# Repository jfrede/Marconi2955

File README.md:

# Marconi 2955 – open firmware

Goal: a functionally equivalent, open re-implementation of the firmware of the Marconi 2955
radio communications test set, with bug fixes and convenience features (quick frequency entry,
user-defined power-on default, plain-text self-test error messages).

## Layout
- `docs/`   – hardware and behaviour specification (own text, publishable)
- `emu/`    – 8085 emulator and instrument peripherals (C)
- `fw/`     – new firmware (C, platform-neutral with a hardware abstraction layer)
- `tools/`  – helper scripts for building and comparing
- `hardware/` – KiCad projects of the add-on boards
- `private/` – original ROMs, manuals, Ghidra project, disassembly. **Not in the repository.**

## Documentation
Start with [docs/architecture.md](docs/architecture.md). The other files in `docs/` explain how
each function works, the registers, the stored data, GPIB, and what is still missing.

## Rules
- Original ROMs, their disassembly and the manual PDFs stay private (see `.gitignore`).
- Only own code and self-written specification are published.
- Before any test on the instrument: back up EEPROM IC13. It holds the calibration data, which
  cannot be recreated. The NOVRAMs hold only the current settings; GPIB `SV` reads them out if
  you want to keep them.

## Licence

- `fw/`, `emu/` and `tools/`: GNU General Public License, version 3 or later (GPL-3.0-or-later). See [LICENSE](LICENSE).
- `docs/`: Creative Commons Attribution 4.0 International (CC BY 4.0). See [docs/LICENSE](docs/LICENSE).
- `hardware/`: CERN Open Hardware Licence Version 2, Strongly Reciprocal (CERN-OHL-S-2.0). See [hardware/LICENSE](hardware/LICENSE).

Original ROMs and manuals are not part of this project and are not covered by these licences.

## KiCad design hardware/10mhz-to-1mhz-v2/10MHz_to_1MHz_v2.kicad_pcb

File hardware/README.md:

# Hardware

Add-on boards for the Marconi 2955, as KiCad projects with Gerber files.

| Folder | Board |
|---|---|
| `step-attenuator/` | Solid-state replacement for the coarse step attenuator |
| `om345-replacement/` | Replacement for the OM345 hybrid amplifier, using a MAR-7SM+ |
| `om345-testrig/` | Test fixture for measuring an OM345 or a replacement board |
| `10mhz-to-1mhz/` | Converts a 10 MHz reference signal to 1 MHz |
| `10mhz-to-1mhz-v2/` | Redesign of the converter with SMD parts and a single 5 V supply (v2.0, not built or tested yet; see its SPEC.md) |
| `cpu-adapter/` | RP2354B board for the 8085 socket, runs the new firmware (v1.0, not built or tested yet; see its SPEC.md) |

## Pictures

### Step attenuator

### OM345 replacement

### 10 MHz to 1 MHz converter

The picture shows the first version, with through-hole parts. It uses a 74LS90, a 2N2369 and a
BC308B and needs -12 V besides +5 V. The second version uses a TLV3501 comparator and a 74HC390
and runs from +5 V alone. Specification and status:
[10mhz-to-1mhz-v2/SPEC.md](10mhz-to-1mhz-v2/SPEC.md).

### CPU adapter

The RP2354B board that replaces the 8085 on AB4. Specification and status:
[cpu-adapter/SPEC.md](cpu-adapter/SPEC.md).

## Licence

The board designs in this folder are open hardware under the CERN Open Hardware Licence
Version 2, Strongly Reciprocal (CERN-OHL-S-2.0). See [LICENSE](LICENSE).

## Note on the MAR-7SM+ footprint

The symbol and footprint library for the MAR-7SM+ is not included, because its licence does not
allow it to be passed on as a library. It comes from SamacSys. The board file still contains the
footprint, so the board opens and can be fabricated as it is. To change the footprint, get the
library for the MAR-7SM+ yourself and add it to the project as a library called `RF`.

## Note on the CPU adapter's libraries and 3D models

The KiCad library for the SN74LVC16245ADGGR (from TI) and the STEP models for the RP2354B, the
TSSOP-48 translators and the USB-C receptacle are not included, because their licences are
unclear or do not allow them to be passed on. The board file still contains all footprints, so
the board opens and can be fabricated as it is; only the 3D view lacks those parts.

## Note on the SMA jacks of the 10 MHz to 1 MHz converter v2

The STEP model of the Amphenol 901-143 SMA jack (`901-143.STEP`, referred to from the project
folder) is not included, because its licence is unclear. Only the 3D view lacks the two jacks.

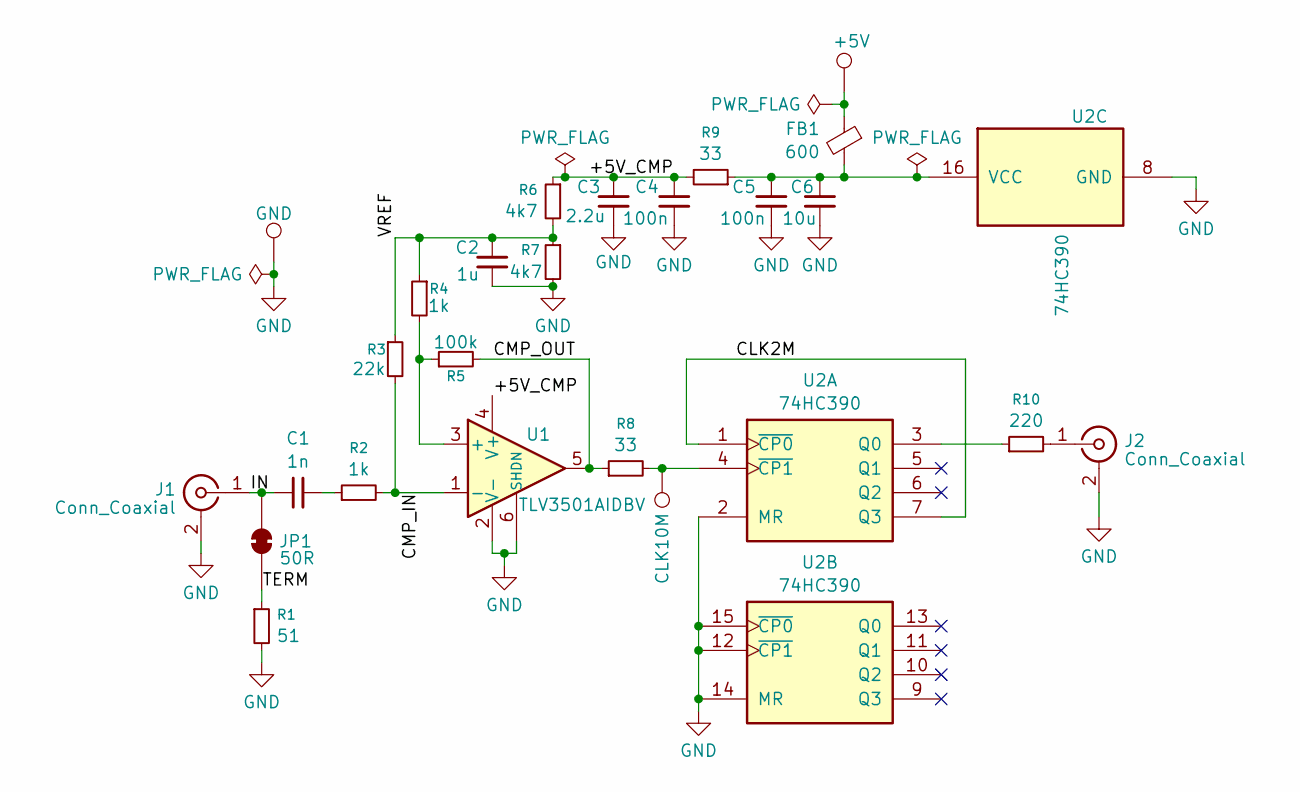
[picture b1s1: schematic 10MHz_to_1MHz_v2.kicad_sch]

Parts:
C1: 1n; C_0603_1608Metric_Pad1.08x0.95mm_HandSolder
C2: 1u; C_0603_1608Metric_Pad1.08x0.95mm_HandSolder
C3: 2.2u; C_0603_1608Metric_Pad1.08x0.95mm_HandSolder
C4, C5: 100n; C_0603_1608Metric_Pad1.08x0.95mm_HandSolder
C6: 10u; C_0805_2012Metric_Pad1.18x1.45mm_HandSolder
FB1: 600; L_0805_2012Metric_Pad1.05x1.20mm_HandSolder
J1, J2: Conn_Coaxial; SMA_Amphenol_901-143_Horizontal
JP1: 50R; SolderJumper-2_P1.3mm_Bridged_Pad1.0x1.5mm
R1: 51; R_0805_2012Metric_Pad1.20x1.40mm_HandSolder
R2, R4: 1k; R_0603_1608Metric_Pad0.98x0.95mm_HandSolder
R3: 22k; R_0603_1608Metric_Pad0.98x0.95mm_HandSolder
R5: 100k; R_0603_1608Metric_Pad0.98x0.95mm_HandSolder
R6, R7: 4k7; R_0603_1608Metric_Pad0.98x0.95mm_HandSolder
R8, R9: 33; R_0603_1608Metric_Pad0.98x0.95mm_HandSolder
R10: 220; R_0603_1608Metric_Pad0.98x0.95mm_HandSolder
TP1: +5V; TestPoint_THTPad_D2.0mm_Drill1.0mm
TP2: GND; TestPoint_THTPad_D2.0mm_Drill1.0mm
TP3: CLK10M; TestPoint_Pad_D1.0mm
U1: TLV3501AIDBV; SOT-23-6
U2: 74HC390; SO-16_3.9x9.9mm_P1.27mm

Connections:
/+5V_CMP: C3.2, C4.2, R6.1, R9.2, U1.4 (V+)
/CLK2M: U2.1 (~CP0), U2.7 (Q3)
/CMP_IN: R2.2, R3.2, U1.1 (-)
/CMP_OUT: R5.2, R8.1, U1.5
/IN: C1.1, J1.1 (In), JP1.2 (B)
/TERM: JP1.1 (A), R1.1
/VREF: C2.2, R3.1, R4.1, R6.2, R7.1
GND: C2.1, C3.1, C4.1, C5.1, C6.1, J1.2 (Ext), J2.2 (Ext), R1.2, R7.2, TP2.1 (1_1), U1.2 (V-), U1.6 (SHDN), U2.2 (MR), U2.8 (GND), U2.12 (~CP1), U2.14 (MR), U2.15 (~CP0)
unnamed: C1.2, R2.1
unnamed: FB1.1, TP1.1 (1_1)
unnamed: J2.1 (In), R10.2
unnamed: R4.2, R5.1, U1.3 (+)
unnamed: R10.1, U2.3 (Q0)
unnamed: R8.2, TP3.1 (1_1), U2.4 (~CP1)
unnamed: C5.2, C6.2, FB1.2, R9.1, U2.16 (VCC)

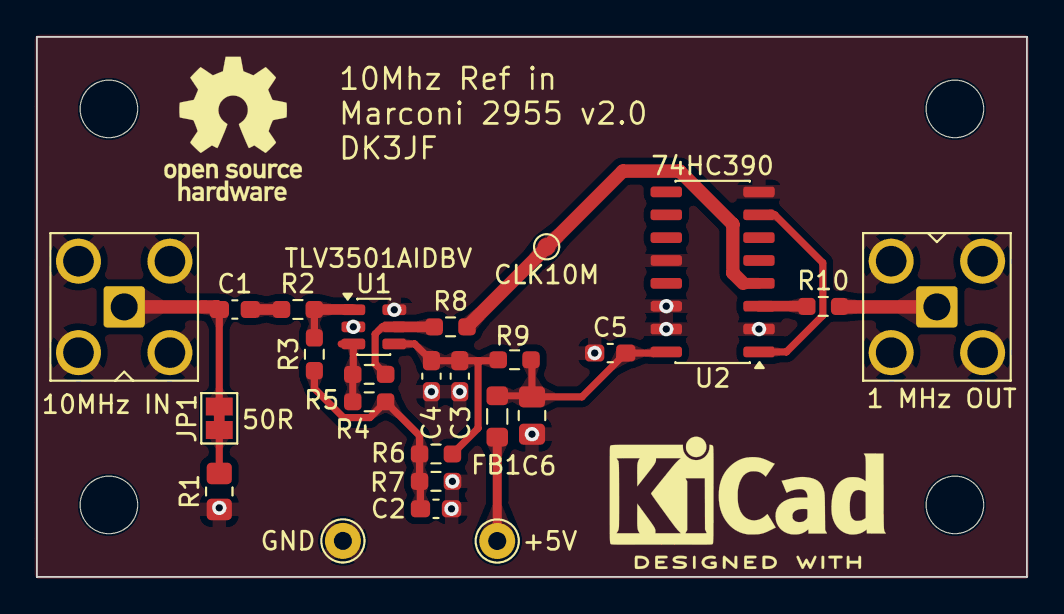
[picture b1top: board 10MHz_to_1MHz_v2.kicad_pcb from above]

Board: 2 copper layers, 55.0 x 30.0 mm, 25 parts (0 on the bottom side), 15 nets.

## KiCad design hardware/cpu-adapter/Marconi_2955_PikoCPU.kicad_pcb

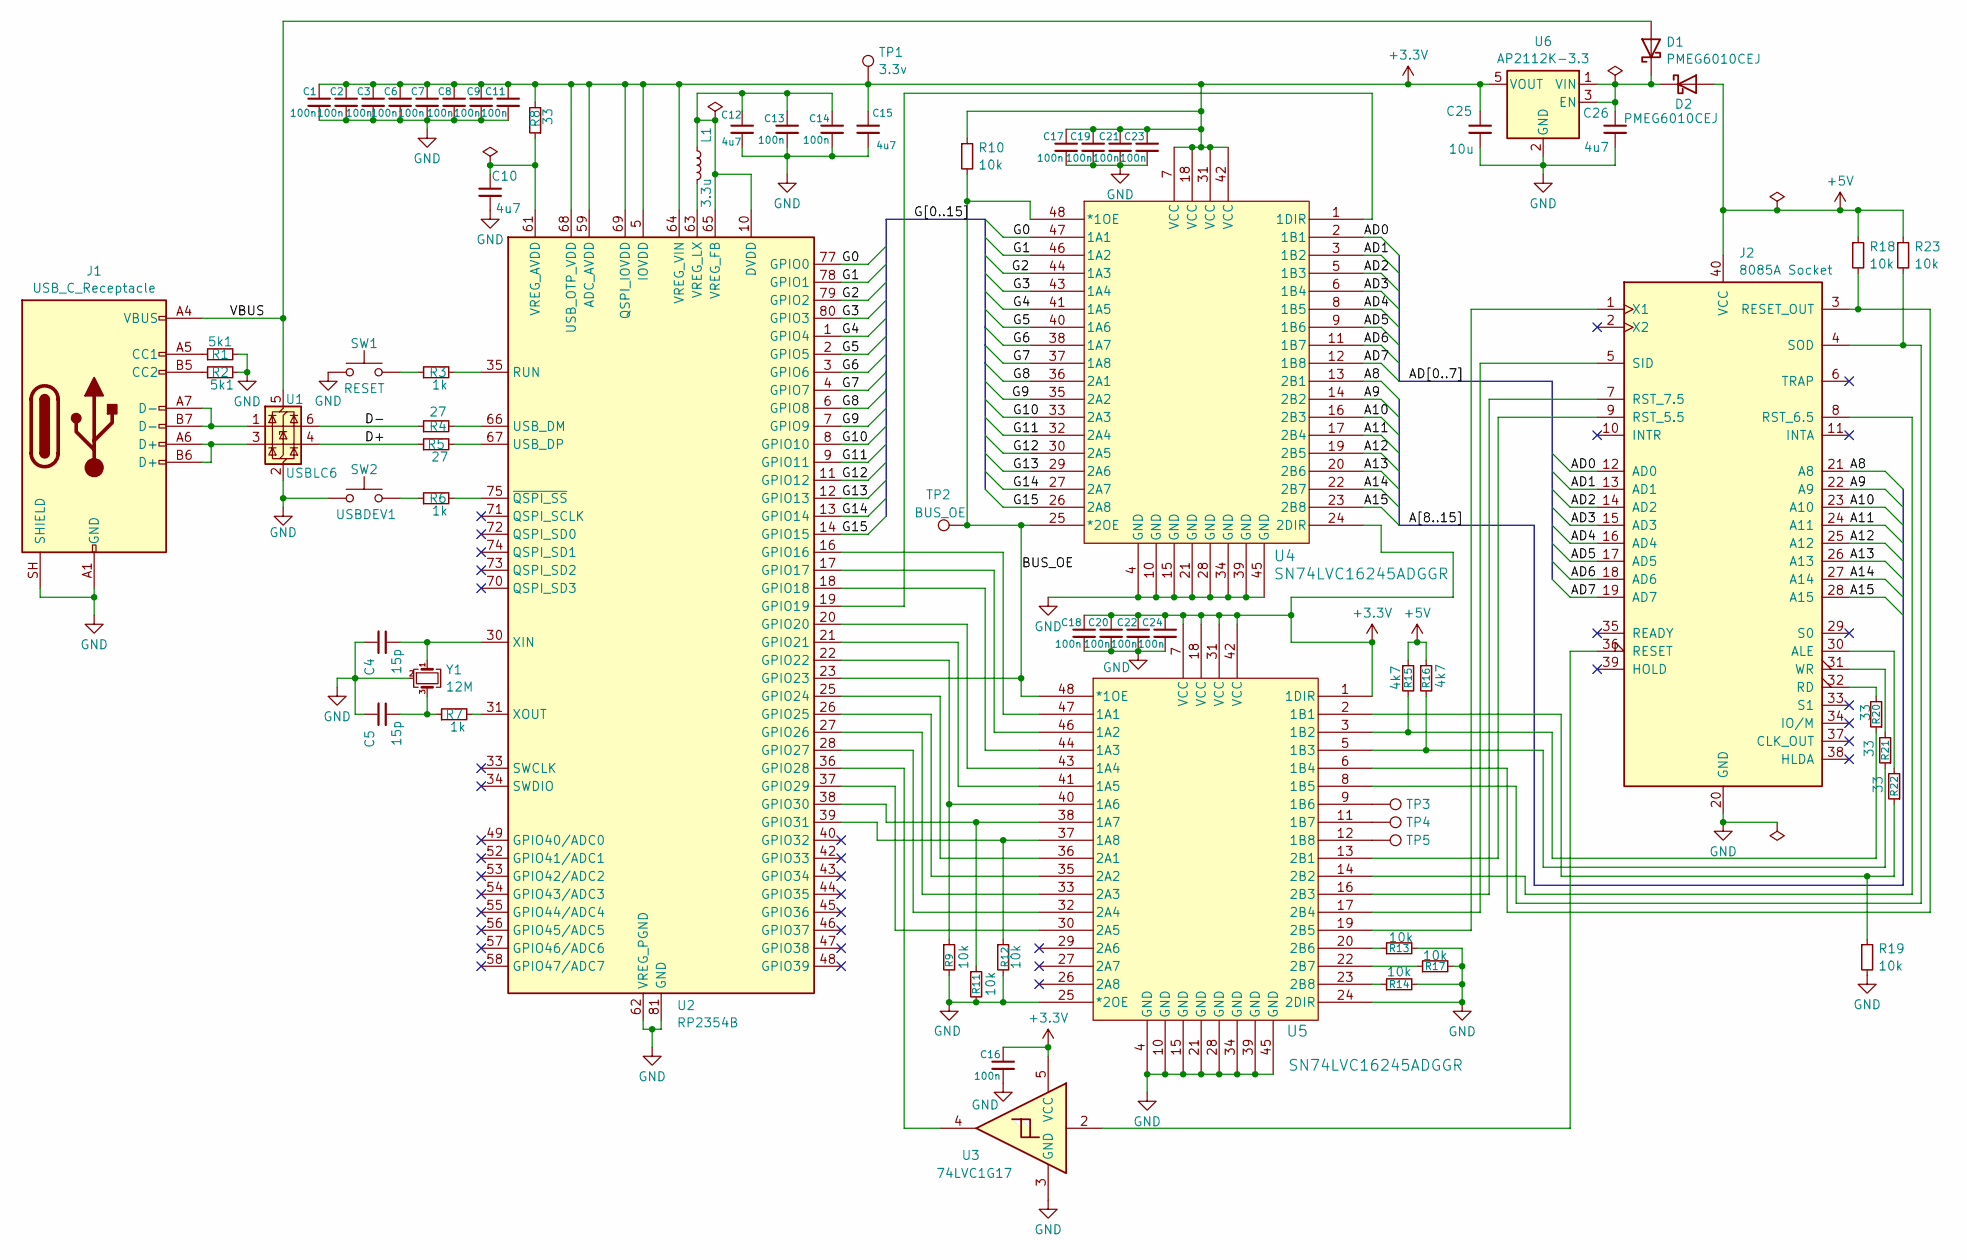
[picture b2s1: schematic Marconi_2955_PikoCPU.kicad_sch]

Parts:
C1, C2, C3, C6, C7, C8, C9, C11, C13, C14, C16, C17, C18, C19, C20, C21, C22, C23, C24: 100n; C_0603_1608Metric_Pad1.08x0.95mm_HandSolder
C4, C5: 15p; C_0603_1608Metric_Pad1.08x0.95mm_HandSolder
C10, C12, C15, C26: 4u7; C_0805_2012Metric_Pad1.18x1.45mm_HandSolder
C25: 10u; C_1210_3225Metric_Pad1.33x2.70mm_HandSolder
D1, D2: PMEG6010CEJ; D_SOD-323
J1: USB_C_Receptacle; USB_C_Receptacle_HRO_TYPE-C-31-M-12
J2: 8085A Socket; DIP-40_W15.24mm
L1: 3.3u; L_0805_2012Metric_Pad1.05x1.20mm_HandSolder
R1, R2: 5k1; R_0603_1608Metric_Pad0.98x0.95mm_HandSolder
R3, R6, R7: 1k; R_0603_1608Metric_Pad0.98x0.95mm_HandSolder
R4, R5: 27; R_0603_1608Metric_Pad0.98x0.95mm_HandSolder
R8, R20, R21, R22: 33; R_0603_1608Metric_Pad0.98x0.95mm_HandSolder
R9, R10, R11, R12, R13, R14, R17, R18, R19, R23: 10k; R_0603_1608Metric_Pad0.98x0.95mm_HandSolder
R15, R16: 4k7; R_0603_1608Metric_Pad0.98x0.95mm_HandSolder
SW1: RESET; SW_SPST_PTS810
SW2: USBDEV1; SW_SPST_PTS810
TP1: 3.3v; TestPoint_Pad_D1.0mm
TP2: BUS_OE; TestPoint_Pad_D1.0mm
TP3, TP4, TP5: TestPoint_Pad_D1.0mm
U1: USBLC6; SOT-23-6
U2: RP2354B; QFN-80-1EP_10x10mm_P0.4mm_EP3.4x3.4mm
U3: 74LVC1G17; SOT-23-5_HandSoldering
U4, U5: SN74LVC16245ADGGR; DGG48
U6: AP2112K-3.3; SOT-23-5
Y1: 12M; Crystal_SMD_3225-4Pin_3.2x2.5mm

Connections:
+3.3V: C1.1, C2.1, C3.1, C6.1, C7.1, C8.1, C9.1, C11.1, C15.2, C16.1, C17.1, C18.1, C19.1, C20.1, C21.1, C22.1, C23.1, C24.1, C25.1, R8.2, R10.1, TP1.1 (1_1), U2.5 (IOVDD), U2.15 (IOVDD), U2.24 (IOVDD), U2.29 (IOVDD), U2.41 (IOVDD), U2.50 (IOVDD), U2.59 (ADC_AVDD), U2.60 (IOVDD), U2.64 (VREG_VIN), U2.68 (USB_OTP_VDD), U2.69 (QSPI_IOVDD), U2.76 (IOVDD), U3.5 (VCC), U4.7 (VCC), U4.18 (VCC), U4.24 (2DIR), U4.31 (VCC), U4.42 (VCC), U5.1 (1DIR), U5.7 (VCC), U5.18 (VCC), U5.31 (VCC), U5.42 (VCC), U6.5 (VOUT)
+5V: D2.2 (A), J2.40 (VCC), R15.1, R16.1, R18.1, R23.1
/A8: J2.21 (A8), U4.13 (2B1)
/A9: J2.22 (A9), U4.14 (2B2)
/A10: J2.23 (A10), U4.16 (2B3)
/A11: J2.24 (A11), U4.17 (2B4)
/A12: J2.25 (A12), U4.19 (2B5)
/A13: J2.26 (A13), U4.20 (2B6)
/A14: J2.27 (A14), U4.22 (2B7)
/A15: J2.28 (A15), U4.23 (2B8)
/AD0: J2.12 (AD0), U4.2 (1B1)
/AD1: J2.13 (AD1), U4.3 (1B2)
/AD2: J2.14 (AD2), U4.5 (1B3)
/AD3: J2.15 (AD3), U4.6 (1B4)
/AD4: J2.16 (AD4), U4.8 (1B5)
/AD5: J2.17 (AD5), U4.9 (1B6)
/AD6: J2.18 (AD6), U4.11 (1B7)
/AD7: J2.19 (AD7), U4.12 (1B8)
/BUS_OE: R10.2, TP2.1 (1_1), U2.23 (GPIO23), U4.25 (*2OE), U4.48 (*1OE), U5.48 (*1OE)
/D+: R5.1, U1.4 (I/O2)
/D-: R4.1, U1.6 (I/O1)
/G0: U2.77 (GPIO0), U4.47 (1A1)
/G1: U2.78 (GPIO1), U4.46 (1A2)
/G2: U2.79 (GPIO2), U4.44 (1A3)
/G3: U2.80 (GPIO3), U4.43 (1A4)
/G4: U2.1 (GPIO4), U4.41 (1A5)
/G5: U2.2 (GPIO5), U4.40 (1A6)
/G6: U2.3 (GPIO6), U4.38 (1A7)
/G7: U2.4 (GPIO7), U4.37 (1A8)
/G8: U2.6 (GPIO8), U4.36 (2A1)
/G9: U2.7 (GPIO9), U4.35 (2A2)
/G10: U2.8 (GPIO10), U4.33 (2A3)
/G11: U2.9 (GPIO11), U4.32 (2A4)
/G12: U2.11 (GPIO12), U4.30 (2A5)
/G13: U2.12 (GPIO13), U4.29 (2A6)
/G14: U2.13 (GPIO14), U4.27 (2A7)
/G15: U2.14 (GPIO15), U4.26 (2A8)
/VBUS: D1.2 (A), J1.A4 (VBUS), J1.A9 (VBUS), J1.B4 (VBUS), J1.B9 (VBUS), U1.5 (VBUS)
GND: C1.2, C2.2, C3.2, C4.1, C5.1, C6.2, C7.2, C8.2, C9.2, C10.1, C11.2, C12.1, C13.2, C14.2, C15.1, C16.2, C17.2, C18.2, C19.2, C20.2, C21.2, C22.2, C23.2, C24.2, C25.2, C26.2, J1.A1 (GND), J1.A12 (GND), J1.B1 (GND), J1.B12 (GND), J1.SH (SHIELD), J2.20 (GND), R1.2, R2.2, R9.2, R11.2, R12.2, R13.2, R14.2, R17.2, R19.2, SW1.1, SW2.1, U1.2 (GND), U2.62 (VREG_PGND), U2.81 (GND), U3.3 (GND), U4.4 (GND), U4.10 (GND), U4.15 (GND), U4.21 (GND), U4.28 (GND), U4.34 (GND), U4.39 (GND), U4.45 (GND), U5.4 (GND), U5.10 (GND), U5.15 (GND), U5.21 (GND), U5.24 (2DIR), U5.25 (*2OE), U5.28 (GND), U5.34 (GND), U5.39 (GND), U5.45 (GND), U6.2 (GND), Y1.2 (G), Y1.4 (G)
unnamed: C5.2, R7.1, Y1.3
unnamed: C26.1, D1.1 (K), D2.1 (K), U6.1 (VIN), U6.3 (EN)
unnamed: J1.A5 (CC1), R1.1
unnamed: J1.B5 (CC2), R2.1
unnamed: J1.A6 (D+), J1.B6 (D+), U1.3 (I/O2)
unnamed: J1.A7 (D-), J1.B7 (D-), U1.1 (I/O1)
unnamed: J2.30 (ALE), R22.2
unnamed: J2.32 (RD), R20.2
unnamed: J2.36 (RESET), U3.2
unnamed: J2.3 (RESET_OUT), R18.2, U5.6 (1B4)
unnamed: J2.9 (RST_5.5), U5.13 (2B1)
unnamed: J2.8 (RST_6.5), U5.14 (2B2)
unnamed: J2.7 (RST_7.5), U5.16 (2B3)
unnamed: J2.5 (SID), U5.17 (2B4)
unnamed: J2.4 (SOD), R23.2, U5.8 (1B5)
unnamed: J2.31 (WR), R21.2
unnamed: J2.1 (X1), U5.19 (2B5)
unnamed: R3.1, SW1.2
unnamed: R6.1, SW2.2
unnamed: U2.16 (GPIO16), U5.47 (1A1)
unnamed: U2.17 (GPIO17), U5.46 (1A2)
unnamed: U2.18 (GPIO18), U5.44 (1A3)
unnamed: U2.19 (GPIO19), U4.1 (1DIR)
unnamed: U2.20 (GPIO20), U5.43 (1A4)
unnamed: U2.21 (GPIO21), U5.41 (1A5)
unnamed: R9.1, U2.22 (GPIO22), U5.40 (1A6)
unnamed: U2.25 (GPIO24), U5.36 (2A1)
unnamed: U2.26 (GPIO25), U5.35 (2A2)
unnamed: U2.27 (GPIO26), U5.33 (2A3)
unnamed: U2.28 (GPIO27), U5.32 (2A4)
unnamed: U2.36 (GPIO28), U3.4
unnamed: U2.37 (GPIO29), U5.30 (2A5)
unnamed: R11.1, U2.38 (GPIO30), U5.38 (1A7)
unnamed: R12.1, U2.39 (GPIO31), U5.37 (1A8)
unnamed: R3.2, U2.35 (RUN)
unnamed: R4.2, U2.66 (USB_DM)
unnamed: R5.2, U2.67 (USB_DP)
unnamed: C10.2, R8.1, U2.61 (VREG_AVDD)
unnamed: C12.2, C13.1, C14.1, L1.1, U2.10 (DVDD), U2.32 (DVDD), U2.51 (DVDD), U2.65 (VREG_FB)
unnamed: L1.2, U2.63 (VREG_LX)
unnamed: C4.2, U2.30 (XIN), Y1.1
unnamed: R7.2, U2.31 (XOUT)
unnamed: R6.2, U2.75 (~QSPI_SS)
unnamed: R19.1, R22.1, U5.2 (1B1)
unnamed: R15.2, R20.1, U5.3 (1B2)
unnamed: R16.2, R21.1, U5.5 (1B3)
unnamed: TP3.1 (1_1), U5.9 (1B6)
unnamed: TP4.1 (1_1), U5.11 (1B7)
unnamed: TP5.1 (1_1), U5.12 (1B8)
unnamed: R13.1, U5.20 (2B6)
unnamed: R17.1, U5.22 (2B7)
unnamed: R14.1, U5.23 (2B8)

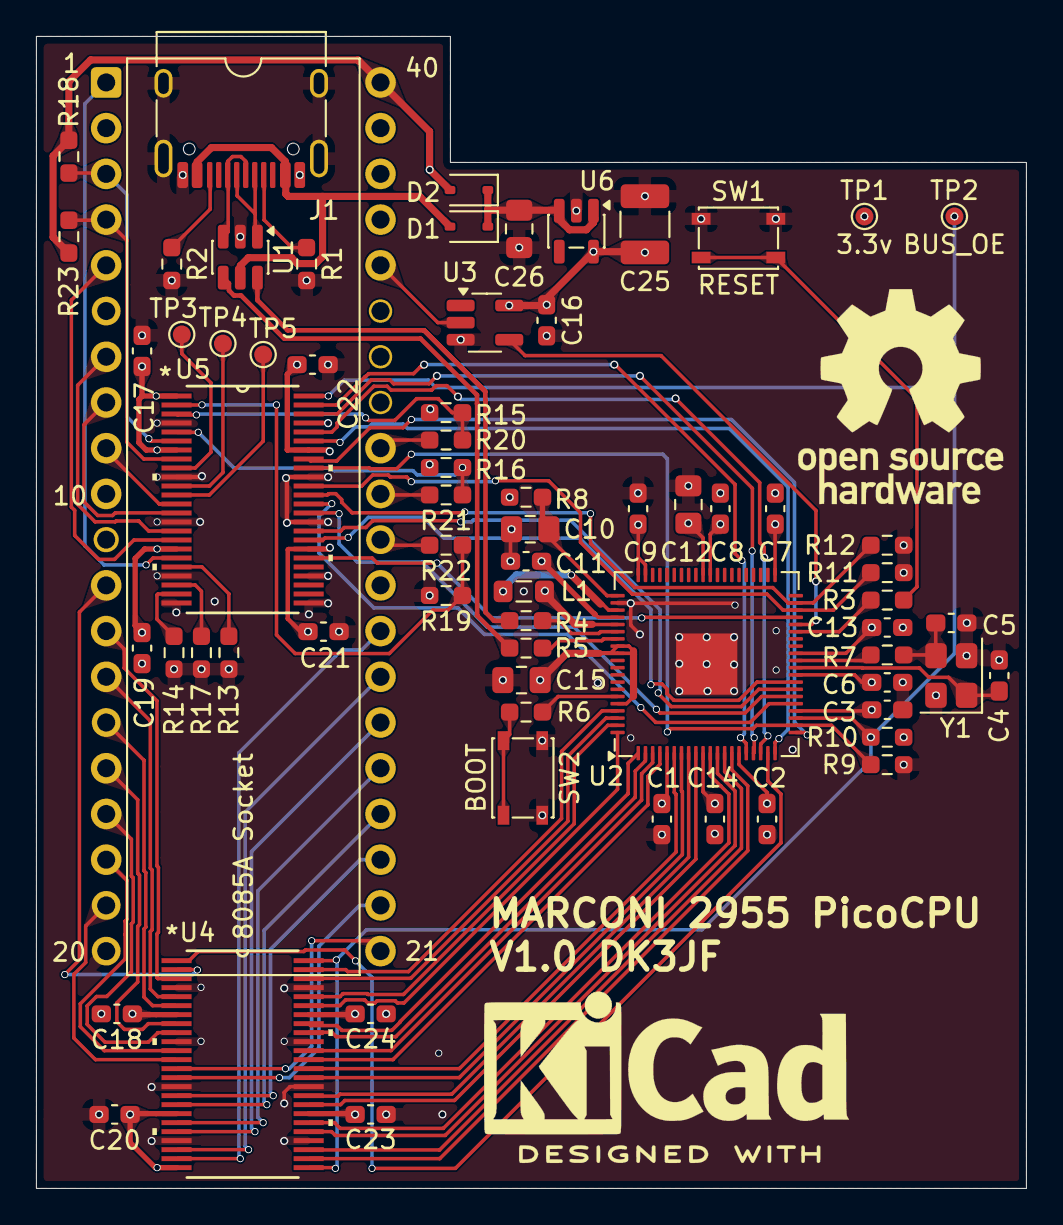
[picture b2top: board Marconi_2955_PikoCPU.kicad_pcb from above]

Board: 4 copper layers, 55.0 x 64.0 mm, 68 parts (0 on the bottom side), 91 nets.

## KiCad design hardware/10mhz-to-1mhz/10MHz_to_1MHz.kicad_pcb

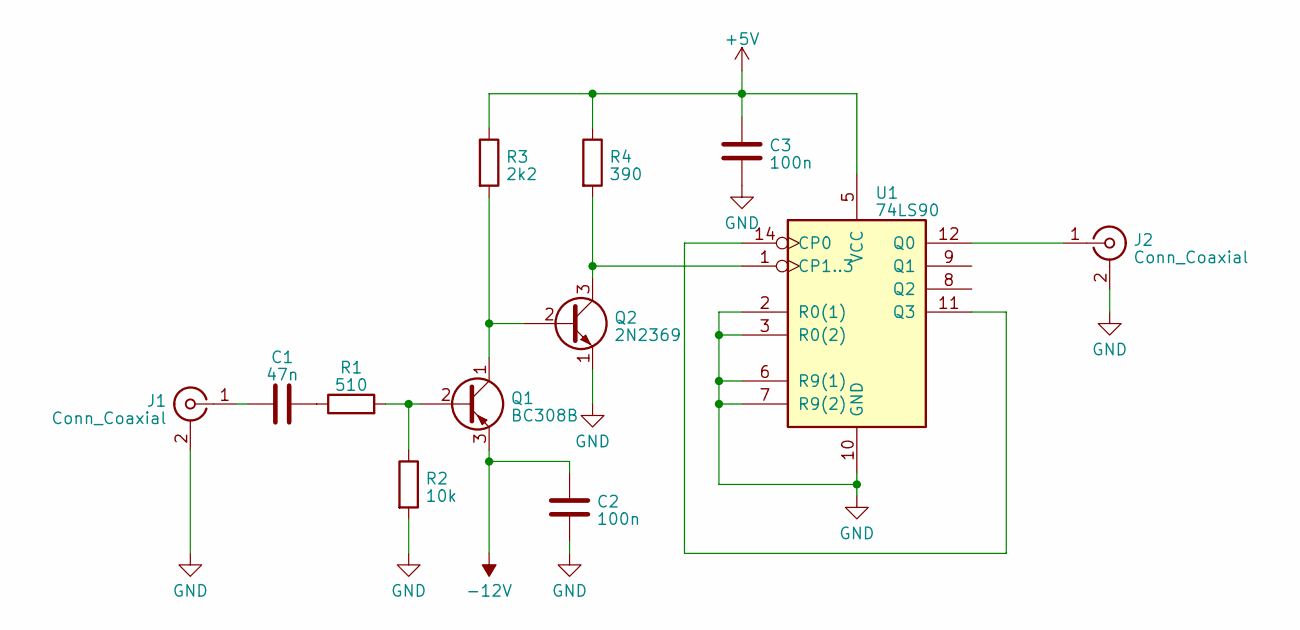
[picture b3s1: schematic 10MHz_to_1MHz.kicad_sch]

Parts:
C1: 47n; C_Disc_D4.7mm_W2.5mm_P5.00mm
C2, C3: 100n; C_Disc_D4.7mm_W2.5mm_P5.00mm
J1, J2: Conn_Coaxial; SMA_Amphenol_901-143_Horizontal
Q1: BC308B; TO-92_Inline
Q2: 2N2369; TO-39-3
R1: 510; R_Axial_DIN0207_L6.3mm_D2.5mm_P10.16mm_Horizontal
R2: 10k; R_Axial_DIN0207_L6.3mm_D2.5mm_P10.16mm_Horizontal
R3: 2k2; R_Axial_DIN0207_L6.3mm_D2.5mm_P10.16mm_Horizontal
R4: 390; R_Axial_DIN0207_L6.3mm_D2.5mm_P10.16mm_Horizontal
U1: 74LS90; DIP-14_W7.62mm

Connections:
+5V: C3.1, R3.1, R4.1, U1.5 (VCC)
-12V: C2.1, Q1.3 (E)
GND: C2.2, C3.2, J1.2 (Ext), J2.2 (Ext), Q2.1 (E), R2.2, U1.2 (R0(1)), U1.3 (R0(2)), U1.6 (R9(1)), U1.7 (R9(2)), U1.10 (GND)
unnamed: C1.2, R1.1
unnamed: C1.1, J1.1 (In)
unnamed: J2.1 (In), U1.12 (Q0)
unnamed: Q1.2 (B), R1.2, R2.1
unnamed: Q1.1 (C), Q2.2 (B), R3.2
unnamed: Q2.3 (C), R4.2, U1.1 (CP1..3)
unnamed: U1.11 (Q3), U1.14 (CP0)

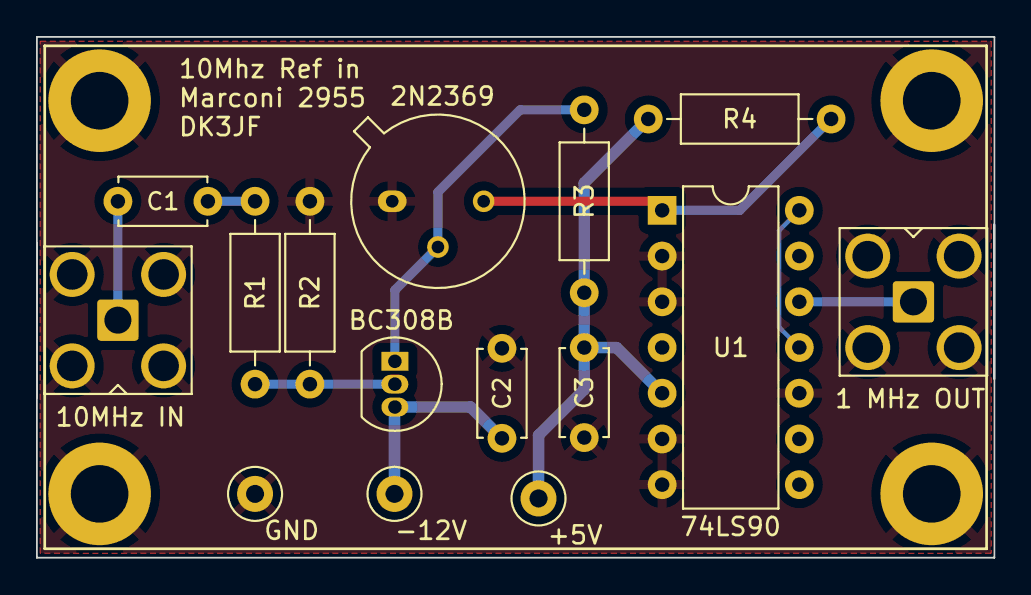
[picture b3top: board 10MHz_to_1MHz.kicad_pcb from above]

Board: 2 copper layers, 53.2 x 28.9 mm, 12 parts (0 on the bottom side), 10 nets.
